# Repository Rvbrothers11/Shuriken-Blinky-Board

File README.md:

# Shuriken-Blinky-Board
A custom built blinky board in the shape of a Shuriken with a custom 3D printed case!

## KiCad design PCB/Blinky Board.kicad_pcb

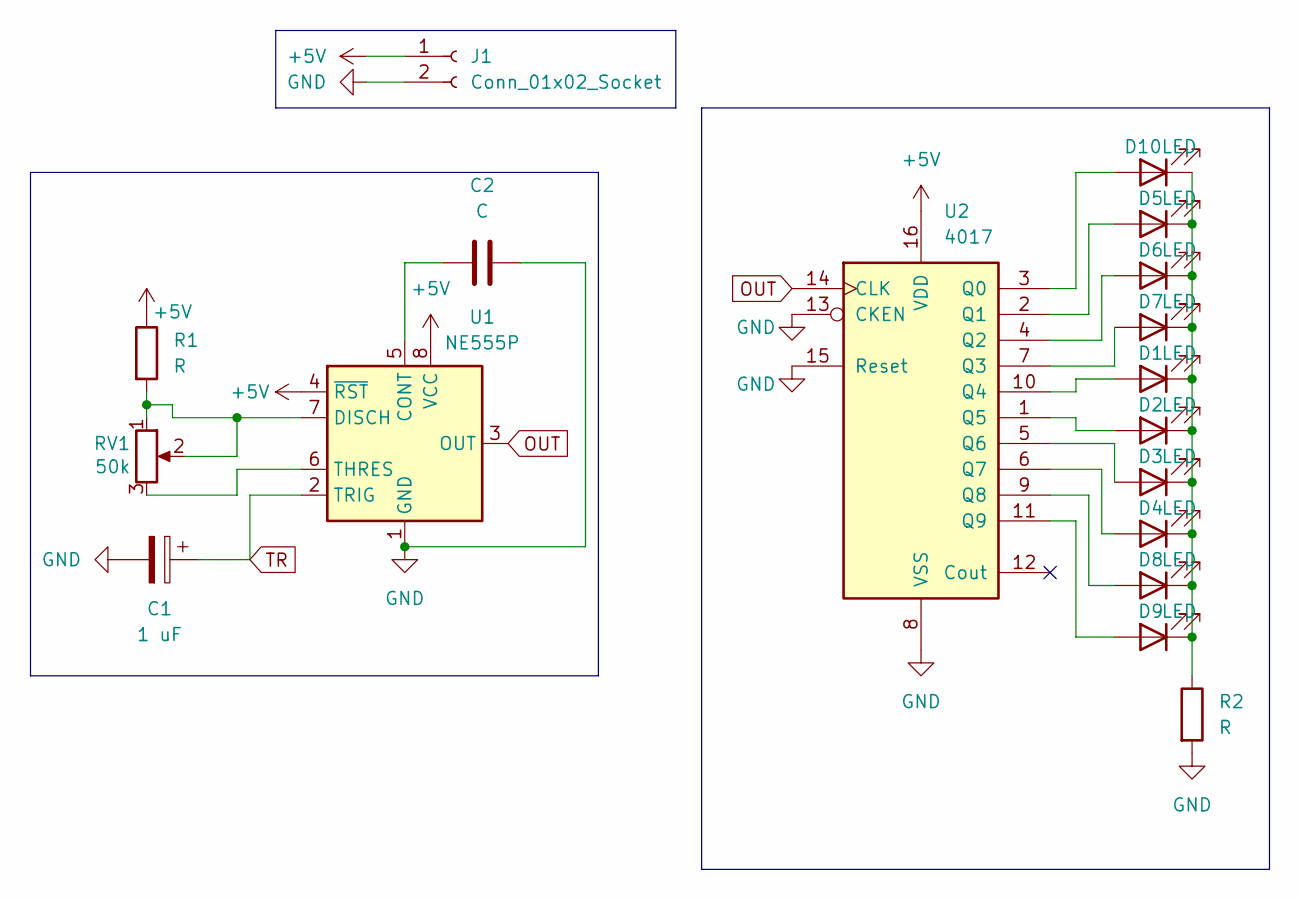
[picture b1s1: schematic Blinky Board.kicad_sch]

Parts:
C1: 1 uF; CP_Radial_D5.0mm_P2.00mm
C2: C; C_Disc_D7.5mm_W2.5mm_P5.00mm
D1, D2, D3, D4, D5, D6, D7, D8, D9, D10: LED; LED_D3.0mm
J1: Conn_01x02_Socket; PinHeader_1x02_P2.54mm_Vertical
R1, R2: R; R_Axial_DIN0207_L6.3mm_D2.5mm_P10.16mm_Horizontal
RV1: 50k; Potentiometer_Vishay_T93YA_Vertical
U1: NE555P; DIP-8_W7.62mm
U2: 4017; N16

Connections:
+5V: J1.1, R1.1, U1.4 (~RST), U1.8 (VCC), U2.16 (VDD)
GND: C1.2, C2.2, J1.2, R2.2, U1.1 (GND), U2.8 (VSS), U2.13 (CKEN), U2.15 (Reset)
unnamed: D1.2 (A), U2.10 (Q4)
unnamed: D1.1 (K), D2.1 (K), D3.1 (K), D4.1 (K), D5.1 (K), D6.1 (K), D7.1 (K), D8.1 (K), D9.1 (K), D10.1 (K), R2.1
unnamed: D2.2 (A), U2.1 (Q5)
unnamed: D3.2 (A), U2.5 (Q6)
unnamed: D4.2 (A), U2.6 (Q7)
unnamed: D5.2 (A), U2.2 (Q1)
unnamed: D6.2 (A), U2.4 (Q2)
unnamed: D7.2 (A), U2.7 (Q3)
unnamed: D8.2 (A), U2.9 (Q8)
unnamed: D9.2 (A), U2.11 (Q9)
unnamed: D10.2 (A), U2.3 (Q0)
unnamed: C2.1, U1.5 (CONT)
unnamed: R1.2, RV1.1, RV1.2, U1.7 (DISCH)
unnamed: RV1.3, U1.6 (THRES)
OUT: U1.3 (OUT), U2.14 (CLK)
TR: C1.1, U1.2 (TRIG)

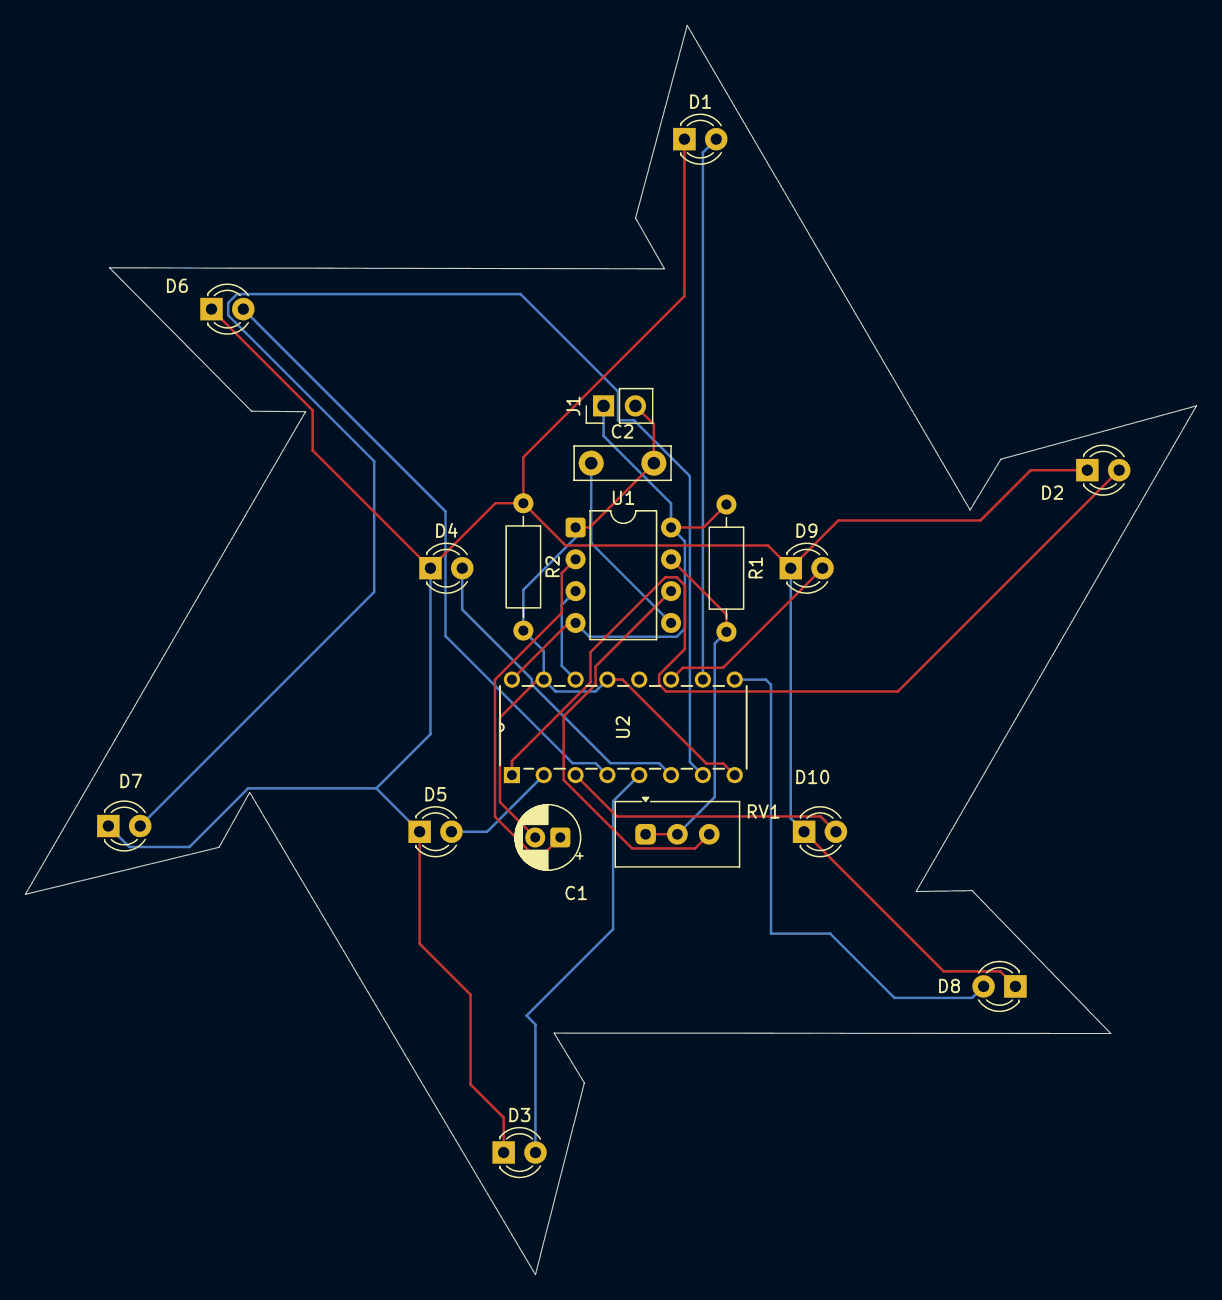
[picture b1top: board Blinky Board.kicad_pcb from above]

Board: 2 copper layers, 93.5 x 99.7 mm, 18 parts (0 on the bottom side), 18 nets.

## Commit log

2026-05-26 Create a
